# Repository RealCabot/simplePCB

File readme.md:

Arduino shield for CaBot
=============================

This shield fits on top of an Arduino Mega. It provides breakouts for the sensors listed below, and fuses to protect the motor driver and motors. The PCB can be connected to a [L298 motor driver](https://solarbotics.com/product/k_cmd/) or a [Sabertooth 2x12 motor driver](https://www.dimensionengineering.com/products/sabertooth2x12).

**Parts list:**
See Excel file: "simple_component_list.xlsx"

**Sensors:**
1) [IMU](https://www.adafruit.com/product/2472)
2) [Touch Sensor](https://www.adafruit.com/product/1982)

**Connections**
1) M1_PWR (motor 1 power) <---> motor 1 positive and negative connections on motor driver
2) M2_PWR (motor 2 power) <---> motor 2 positive and negative connections on motor driver
3) GND (next to 5V) <---> GND on motor driver (this should be common GND)
4) 12V <---> 12V power supply
5) GND (next to 12V) <---> GND of 12V power supply (this should be common GND)
6) Connect Arduino's digital pins to the appropriate inputs on the motor driver. The pins will be different depending on whether you're using the L298 or Sabertooth (RTFM).
**If the motors are running the wrong direction, reverse the polarity**

**Known Issues**

1) The Arduino may disconnect from the laptop when running rosserial. Unfortunately, I don't know what's causing this. This has only happened once during our testing.
2) Current spikes may cause the fuse to blow (CaBot will stop moving). You must replace the 12V fuse if this happens. **You MUST use a 3A fuse with the L298 Motor Driver, otherwise it will burn out.** The Sabertooth can use up to a 20A fuse.

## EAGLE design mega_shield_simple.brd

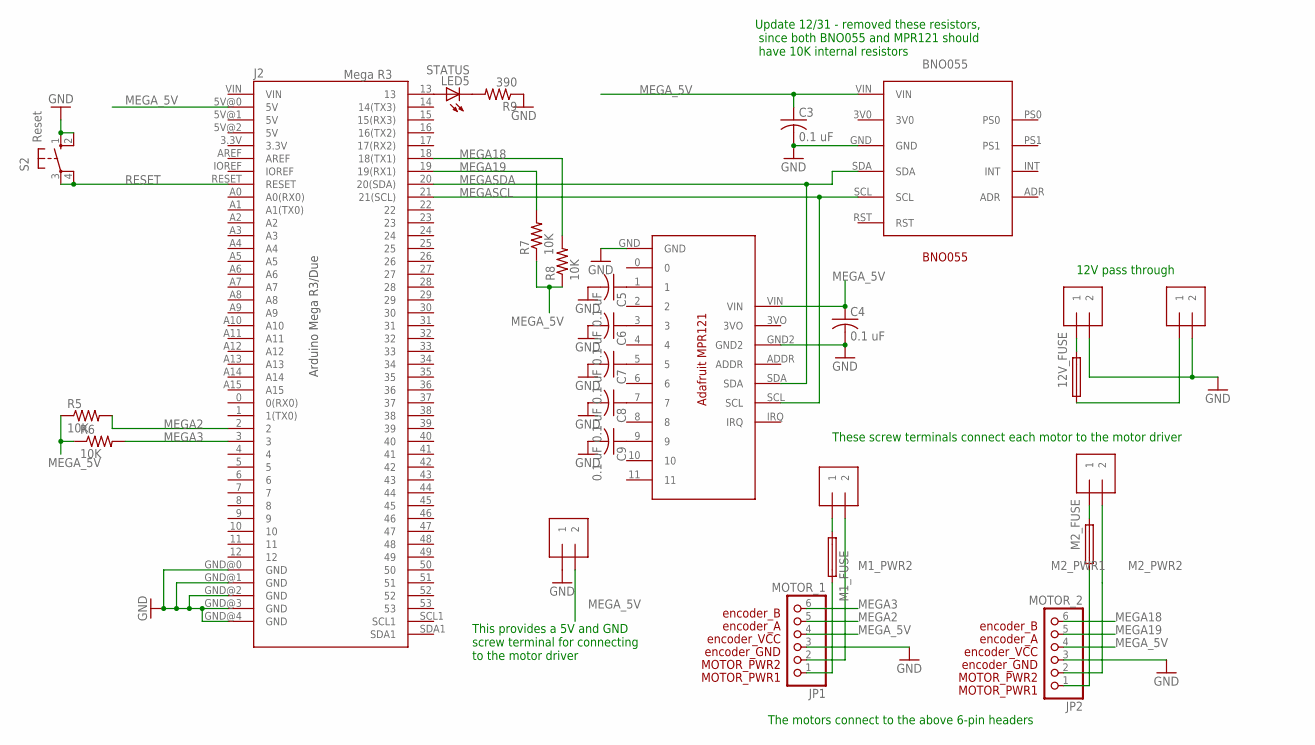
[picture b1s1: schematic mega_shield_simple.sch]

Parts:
5V_OUT, 12V_PASS1, 12V_PASS2: 1X2-3.5MM
12V_FUSE: 3568
BNO055: BNO055
C3, C4, C5, C6, C7, C8, C9: 0.1 uF; C025-050X050
J2: Mega R3; ARDUINO_MEGA
JP1: MOTOR_1; 1X06
JP2: MOTOR_2; 1X06
LED5: STATUS; LED3MM
M1_FUSE, M2_FUSE: FUSETE5; TE5
M1_PWR, M2_PWR: 1X2-3.5MM
MPR121: ADA_MPR121
R5, R6, R7, R8: 10K; 0207/10
R9: 390; 0207/10
S2: Reset; B3F-10XX

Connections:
12V_PASSTHRU1: 12V_FUSE.1, 12V_FUSE.2 (1), 12V_PASS2.1
12V_PASSTHRU2: 12V_FUSE.3 (2), 12V_FUSE.4 (2), 12V_PASS1.1
GND: 5V_OUT.1, 12V_PASS1.2, 12V_PASS2.2, BNO055.GND, C3.2, C4.2, C5.2, C6.2, C7.2, C8.2, C9.2, J2.GND@0 (GND), J2.GND@1 (GND), J2.GND@2 (GND), J2.GND@3 (GND), J2.GND@4 (GND), JP1.3, JP2.3, MPR121.GND, MPR121.GND2, R9.1, S2.1 (S), S2.2 (S1)
M1_PWR1: JP1.1, M1_FUSE.2
M1_PWR2: JP1.2, M1_PWR.2
M2_PWR1: JP2.1, M2_FUSE.2
M2_PWR2: JP2.2, M2_PWR.2
MEGA2: J2.2, JP1.5, R5.2
MEGA3: J2.3, JP1.6, R6.2
MEGA18: J2.18 (18(TX1)), JP2.6, R8.2
MEGA19: J2.19 (19(RX1)), JP2.5, R7.2
MEGASCL: BNO055.SCL, J2.21 (21(SCL)), MPR121.SCL
MEGASDA: BNO055.SDA, J2.20 (20(SDA)), MPR121.SDA
MEGA_5V: 5V_OUT.2, BNO055.VIN, C3.1, C4.1, J2.5V@0 (5V), JP1.4, JP2.4, MPR121.VIN, R5.1, R6.1, R7.1, R8.1
unnamed: C5.1, MPR121.1
unnamed: C6.1, MPR121.3
unnamed: J2.13, LED5.A
unnamed: LED5.K (C), R9.2
unnamed: C7.1, MPR121.5
unnamed: C8.1, MPR121.7
unnamed: M2_FUSE.1, M2_PWR.1
unnamed: C9.1, MPR121.9
unnamed: M1_FUSE.1, M1_PWR.1
RESET: J2.RESET, S2.3, S2.4 (P1)

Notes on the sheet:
Arduino Mega R3/Due
Update 12/31 - removed these resistors, since both BNO055 and MPR121 should have 10K internal resistors
This provides a 5V and GND screw terminal for connecting to the motor driver
These screw terminals connect each motor to the motor driver
The motors connect to the above 6-pin headers
12V pass through

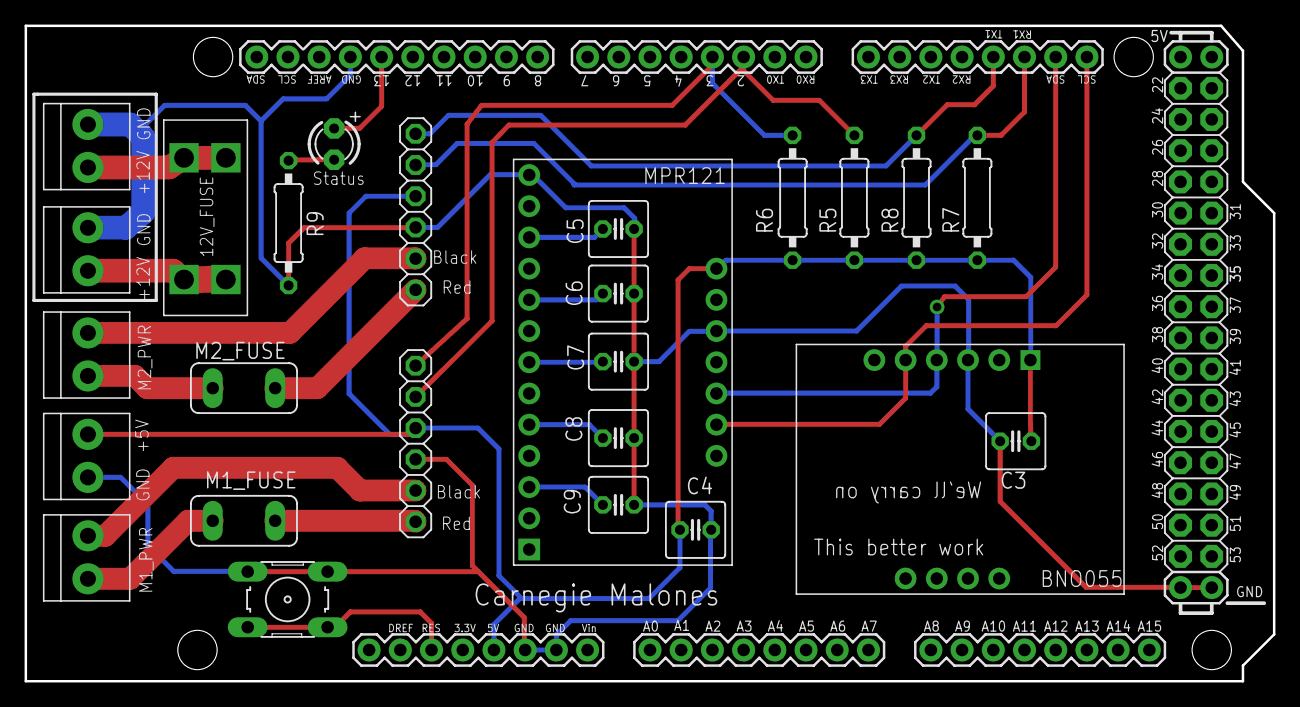
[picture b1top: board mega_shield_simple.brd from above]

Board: 2 copper layers, 101.6 x 53.3 mm, 27 parts (0 on the bottom side), 24 nets.

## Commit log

2018-05-08 add fuses to sch and brd files
2018-05-08 Added gerber files
